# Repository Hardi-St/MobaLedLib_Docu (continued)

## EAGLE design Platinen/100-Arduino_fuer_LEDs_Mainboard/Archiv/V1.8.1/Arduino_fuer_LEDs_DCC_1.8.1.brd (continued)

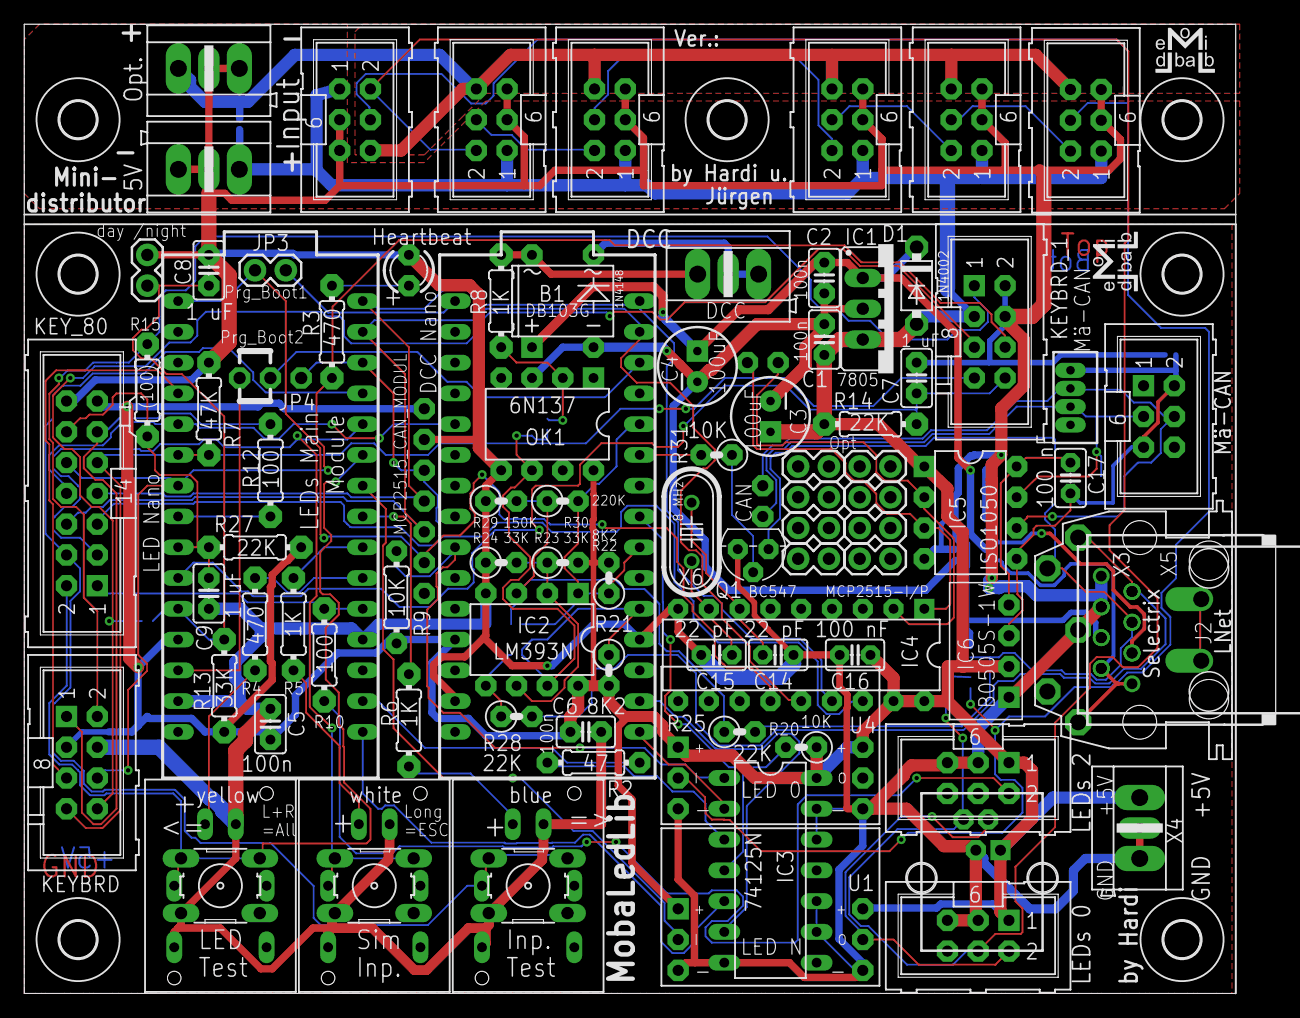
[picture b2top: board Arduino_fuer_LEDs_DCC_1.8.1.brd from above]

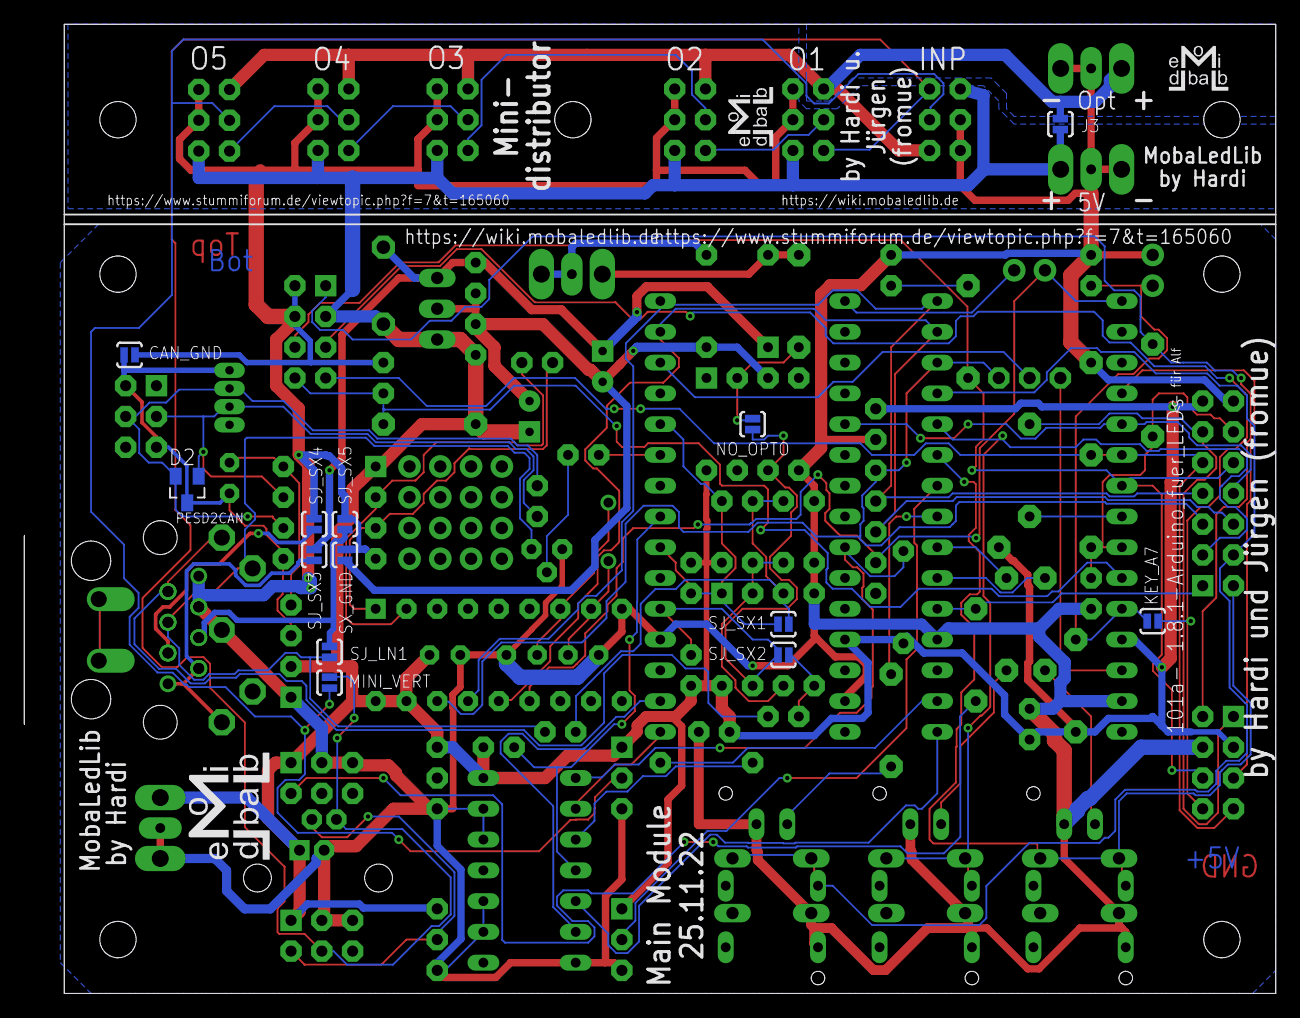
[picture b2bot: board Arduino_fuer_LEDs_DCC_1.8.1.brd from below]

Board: 2 copper layers, 103.3 x 80.0 mm, 113 parts (13 on the bottom side), 74 nets.
